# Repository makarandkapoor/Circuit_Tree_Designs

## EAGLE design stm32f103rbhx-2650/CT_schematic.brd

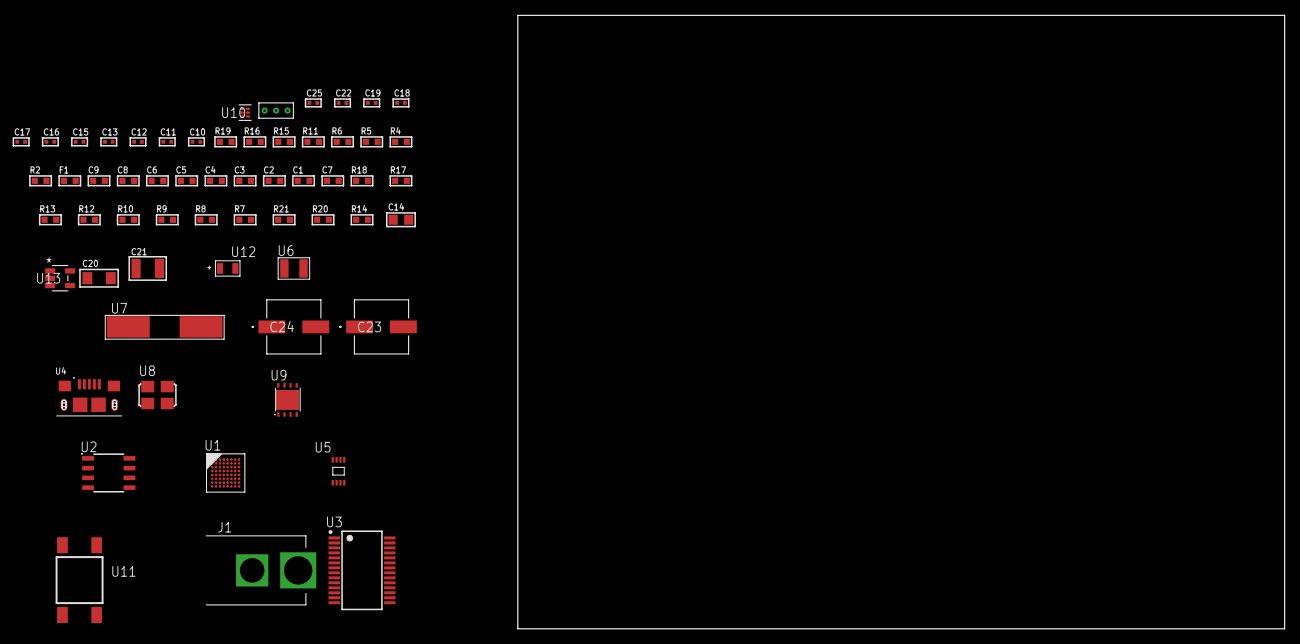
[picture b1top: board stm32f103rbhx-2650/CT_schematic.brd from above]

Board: 2 copper layers, 159.4 x 80.0 mm, 60 parts (0 on the bottom side), 35 nets, no tracks yet.

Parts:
C1, C9: 1e-06; C0603
C2, C3, C4, C5, C6: 1e-07; C0603
C7: 4.7e-06; C0603
C8: 1e-08; C0603
C10, C11: 1e-11; C0402
C12, C17, C18, C19, C25: 1e-08; C0402
C13, C15, C16, C22: 1e-07; C0402
C14: 4.7e-06; C0805
C20: 1e-05; C1206
C21: 1e-05; C1210
C23, C24: 0.0001; EXV-9H
F1: 240.0; L0603
J1: PJ-037B; PJ-037B_PACKAGE
R2, R16: 1000.0; R0603
R4, R11: 4700.0; R0603
R5, R6: 2200.0; R0603
R7, R8, R9, R10, R12, R13, R17, R18: 10000.0; R0603
R14: 100000.0; R0603
R15: 2231.0; R0603
R19: 9100.0; R0603
R20: 680000.0; R0603
R21: 120000.0; R0603
U1: stm32f103rbh6; TFBGA64
U2: AT25M02-SSHD-T; SOIC-8
U3: FT232RL-REEL; SSOP-28
U4: 10118193-0001LF; FCI_10118193-0001LF
U5: 24AA01T-I/MNY; TDFN-8/6MM
U6: ABS07-32.768KHZ-7-T
U7: ABLS-12.000MHZ-B4-T
U8: ASFL1-25MHZ-NCS; ASFL1
U9: LP3878SDX-ADJ/NOPB; WSON-8
U10: TPS3895ADRYR; SON-6
U11: 4-1437565-2; SW_4-1437565-2
U12: Q65110A2395; LGM67K-G1J2-24-Z
U13: nc7sz125m5x; NC7SZ125M5X
U14: Dummy; DUMMY_PACKAGE_127

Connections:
CLK_CRYSTAL_U1_A1: C10.1, U1.A1, U6.1
CLK_CRYSTAL_U1_B1: C11.1, U1.B1, U6.2
CLK_CRYSTAL_U3_27: U3.27, U7.1
CLK_CRYSTAL_U3_28: U3.28, U7.2
CLK_U1_C1: U1.C1, U8.3
GND: C1.2, C2.2, C3.2, C4.2, C5.2, C6.2, C7.2, C8.2, C9.2, C10.2, C11.2, C12.2, C13.2, C14.2, C15.2, C16.2, C17.2, C18.2, C19.2, C20.2, C21.2, C22.2, C23.2, C24.2, C25.2, J1.2, R2.2, R7.2, R13.2, R16.2, R19.2, R21.2, U1.C2, U1.D4, U1.D5, U1.D6, U1.F1, U2.4, U3.7, U3.18, U3.21, U3.25, U3.26, U4.5, U4.6, U4.7, U4.8, U4.9, U5.4, U5.7, U8.2, U9.3, U9.PAD, U10.2, U12.C, U13.1, U13.3, U14.1
NET_U1_A3: R6.1, U1.A3, U5.5
NET_U1_B3: R5.1, U1.B3, U5.6
NET_U1_B4: R7.1, U1.B4
NET_U1_E1: R4.1, U1.E1, U13.4
NET_U1_H1: C8.1, C9.1, F1.1, U1.G1, U1.H1
NET_U1_H8: U11.3, U11.4
NET_U2_3: R8.1, U2.3
NET_U2_7: R10.1, U2.7
NET_U3_14: R12.1, U3.14
NET_U3_17: C15.1, U3.17
NET_U3_19: R13.1, U3.19
NET_U4_1: R11.1, U4.1
NET_U4_2: U3.16, U4.2
NET_U4_3: U3.15, U4.3
NET_U9_1: C19.1, U9.1
NET_U9_6: R15.2, R16.1, U9.6
NET_U9_8: R14.1, U9.8
NET_U10_1: R18.1, R19.1, U10.1
NET_U10_3: R20.2, R21.1, U10.3
NET_U10_4: R17.1, U10.4, U13.2
NET_U11_1: R2.1, U11.1, U11.2
PROC_SPI1_MISO: U1.A4, U2.2
PROC_SPI1_MOSI: U1.C4, U2.5
PROC_SPI1_NSS: R9.1, U1.A6, U2.1
PROC_SPI1_SCK: U1.A5, U2.6
PROC_TIM1_CH2N: U1.F5, U14.2
PROC_TIM1_CH3: U1.C6, U14.3
VCC_S1_6V7: C20.1, C23.1, C24.1, J1.1, R14.2, U9.4
VCC_TIER1_3V3: C1.1, C2.1, C3.1, C4.1, C5.1, C6.1, C7.1, C12.1, C13.1, C14.1, C16.1, C17.1, C18.1, C21.1, C22.1, C25.1, F1.2, R4.2, R5.2, R6.2, R8.2, R9.2, R10.2, R12.2, R15.1, R17.2, R18.2, R20.1, U1.B2, U1.D2, U1.E4, U1.E5, U1.E6, U2.8, U3.4, U3.20, U5.8, U8.4, U9.5, U10.6, U13.5

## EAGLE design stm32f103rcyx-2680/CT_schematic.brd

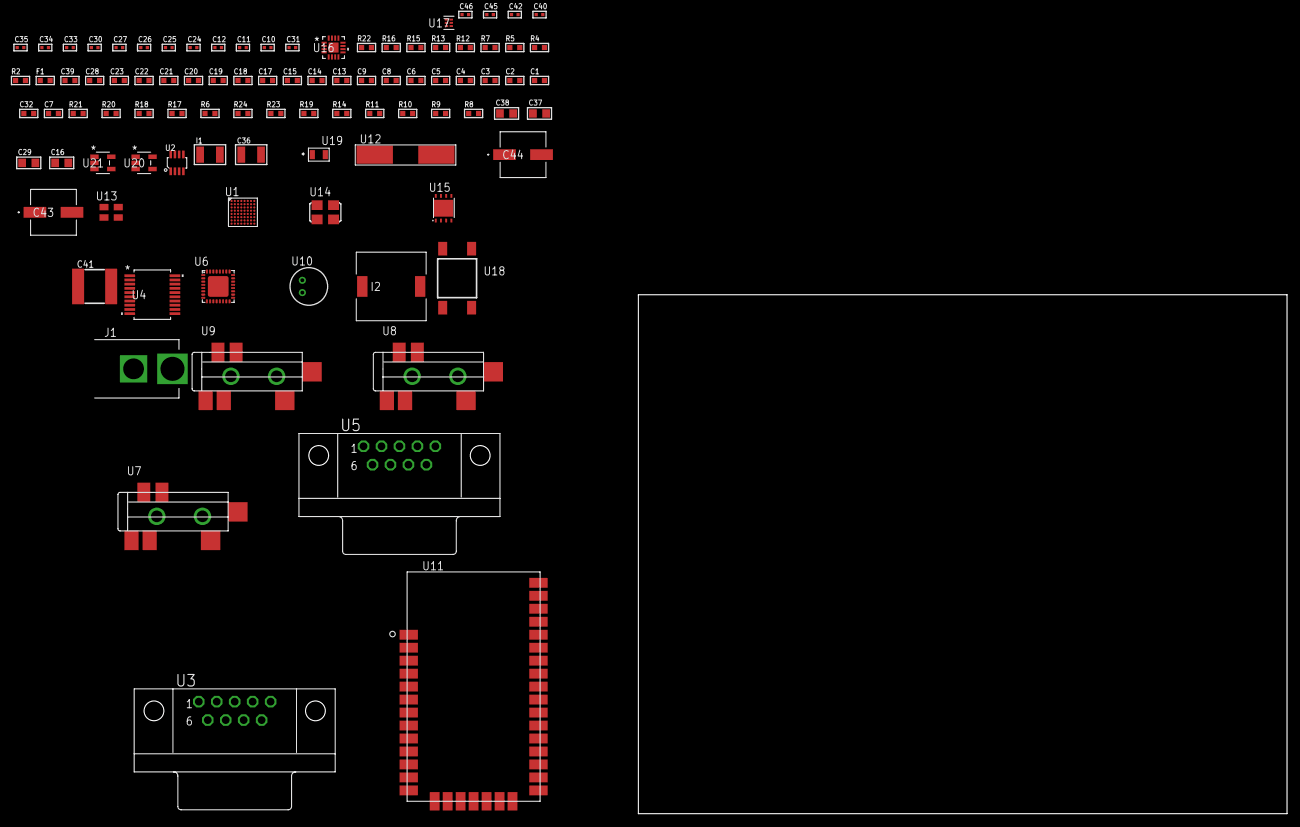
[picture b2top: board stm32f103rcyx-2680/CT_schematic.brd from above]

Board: 2 copper layers, 100.0 x 80.0 mm, 93 parts (0 on the bottom side), 66 nets, no tracks yet.

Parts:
C1, C9, C13, C14, C15, C17, C18, C19, C20, C21, C22, C23, C28, C39: 1e-06; C0603
C2, C3, C4, C5, C6: 1e-07; C0603
C7: 4.7e-06; C0603
C8: 1e-08; C0603
C10, C11: 1e-11; C0402
C12, C24, C25, C26, C27, C30, C40, C42: 1e-07; C0402
C16: 4.7e-06; C0805
C29, C37, C38: 1e-05; C0805
C31: 4.7e-11; C0402
C32: 8.2e-12; C0603
C33, C34, C35, C45, C46: 1e-08; C0402
C36: 1e-05; C1210
C41: 6.8e-05; 2220
C43, C44: 0.0001; EXV-9H
F1: 240.0; L0603
I1: 1.5e-05; L1210
I2: 5.2e-06; DR1040
J1: PJ-037B; PJ-037B_PACKAGE
R2, R16: 1000.0; R0603
R4, R5: 4700.0; R0603
R6, R20, R21: 10000.0; R0603
R7: 120.0; R0603
R8, R9, R10, R11, R14: 100000.0; R0603
R12, R13: 1270.0; R0603
R15: 200.0; R0603
R17: 20000.0; R0603
R18: 91000.0; R0603
R19: 300000.0; R0603
R22: 9100.0; R0603
R23: 680000.0; R0603
R24: 120000.0; R0603
U1: stm32f103rcy7; WLCSP64
U2: MAX3051EKA+T; SOT-23-8
U3, U5: 182-009-113R531; 182-009-MALE
U4: MAX3218EAP+T; SSOP-20
U6: SGTL5000XNAA3; QFN-32
U7, U8, U9: SJ-43515TS-SMT-TR
U10: WM-64PCT; WM-64PC
U11: XB24CZ7UIS-004
U12: ABLS-25.000MHZ-B2F-T
U13: ASEK-32.768KHz-ECST; ASEK
U14: ASFL-24.57MHZ-NCS; ASFL1
U15: LP3878SDX-ADJ/NOPB; WSON-8
U16: LTC3601EUD#PBF; QFN-16_EP
U17: TPS3895ADRYR; SON-6
U18: 4-1437565-2; SW_4-1437565-2
U19: Q65110A2395; LGM67K-G1J2-24-Z
U20, U21: nc7sz125m5x; NC7SZ125M5X

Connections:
CLK_CRYSTAL_U1_D7: C10.1, U1.D7, U12.1
CLK_CRYSTAL_U1_D8: C11.1, U1.D8, U12.2
CLK_U1_B8: U1.B8, U13.3
CLK_U6_21: U6.21, U14.3
GND: C1.2, C2.2, C3.2, C4.2, C5.2, C6.2, C7.2, C8.2, C9.2, C10.2, C11.2, C12.2, C13.2, C14.2, C15.2, C24.2, C25.2, C26.2, C27.2, C28.2, C29.2, C30.2, C31.2, C32.2, C33.2, C34.2, C35.2, C36.2, C37.2, C38.2, C39.2, C41.1, C41.2, C42.2, C43.2, C44.2, C45.2, C46.2, J1.2, R2.2, R6.2, R8.2, R13.2, R16.2, R17.2, R19.2, R22.2, R24.2, U1.A7, U1.B1, U1.E7, U1.F5, U1.H2, U2.2, U3.5, U4.5, U4.17, U4.20, U5.5, U6.1, U6.3, U6.7, U6.EXP, U8.1, U9.1, U10.2, U11.1, U11.11, U11.13, U11.22, U11.35, U13.2, U14.2, U15.3, U15.PAD, U16.1, U16.9, U16.17, U17.2, U19.C, U20.1, U20.3, U21.1, U21.3
NET_U1_A6: R6.1, U1.A6
NET_U1_C7: R5.1, U1.C7, U21.4
NET_U1_G8: C8.1, C9.1, F1.1, U1.F7, U1.G8
NET_U1_H8: U18.3, U18.4
NET_U2_6: R7.2, U2.6
NET_U2_8: R8.1, U2.8
NET_U3_2: R7.2, U2.6, U3.2
NET_U3_3: R7.1, U2.7, U3.3
NET_U4_1: I1.1, U4.1
NET_U4_2: R9.1, U4.2
NET_U4_3: R10.1, U4.3
NET_U4_4: R11.1, U4.4
NET_U4_15: C15.1, U4.15
NET_U4_16: C16.2, U4.16
NET_U4_18: C16.1, U4.18
NET_U4_19: C14.1, U4.19
NET_U5_2: U4.12, U5.2
NET_U5_3: U4.14, U5.3
NET_U5_7: U4.11, U5.7
NET_U5_8: U4.13, U5.8
NET_U6_10: C27.1, U6.10
NET_U6_29: R12.1, U6.29
NET_U6_31: R13.1, U6.31
NET_U7_1: U6.4, U7.1
NET_U7_2: U6.2, U7.2
NET_U7_5: U6.6, U7.5
NET_U8_2: C18.1, U8.2
NET_U8_5: C17.1, U8.5
NET_U9_2: C20.1, C21.1, U9.2
NET_U9_5: C19.1, U9.5
NET_U9_13: C20.2, C21.2
NET_U10_1: C22.1, C23.1, C28.1, U6.16, U10.1
NET_U10_15: C22.2, C23.2
NET_U11_6: R4.1, U11.6, U20.4
NET_U15_1: C35.1, U15.1
NET_U15_6: R15.2, R16.1, U15.6
NET_U15_8: R14.1, U15.8
NET_U16_3: C40.2, I2.1, U16.3, U16.4
NET_U16_6: C40.1, U16.6
NET_U16_7: C39.1, U16.7, U16.12
NET_U16_10: R19.1, U16.10
NET_U16_11: R17.1, R18.1, U16.11
NET_U16_ATNET_3: I2.2, R18.2
NET_U17_1: R21.1, R22.1, U17.1
NET_U17_3: R23.2, R24.1, U17.3
NET_U17_4: R20.1, U17.4, U20.2, U21.2
NET_U18_1: R2.1, U18.1, U18.2
PROC_CAN_RX: U1.C1, U2.4
PROC_CAN_TX: U1.B6, U2.1
PROC_I2S2_CK: U1.G1, U6.24
PROC_I2S2_SD: U1.F1, U6.26
PROC_I2S2_WS: U1.G2, U6.23
PROC_SPI1_MISO: U1.B4, U11.17
PROC_SPI1_MOSI: U1.A5, U11.16
PROC_SPI1_NSS: U1.C3, U11.15
PROC_SPI1_SCK: U1.A4, U11.14
PROC_UART4_RX: U1.B3, U4.9
PROC_UART4_TX: U1.A2, U4.7
VCC_S1_13V0: C36.1, C38.1, C43.1, C44.1, J1.1, R14.2, U15.4, U16.15, U16.16
VCC_TIER1_1V2: C24.1, C37.1, R15.1, U6.30, U15.5
VCC_TIER1_3V3: C1.1, C2.1, C3.1, C4.1, C5.1, C6.1, C7.1, C12.1, C13.1, C25.1, C26.1, C29.1, C30.1, C31.1, C32.1, C33.1, C34.1, C41.2, C42.1, C45.1, C46.1, F1.2, I1.2, I2.2, R4.2, R5.2, R9.2, R10.2, R11.2, R12.2, R18.2, R20.2, R21.2, R23.1, U1.A1, U1.A8, U1.C6, U1.G6, U1.H1, U2.3, U4.6, U6.5, U6.20, U11.2, U11.27, U13.4, U14.4, U16.8, U17.6, U20.5, U21.5

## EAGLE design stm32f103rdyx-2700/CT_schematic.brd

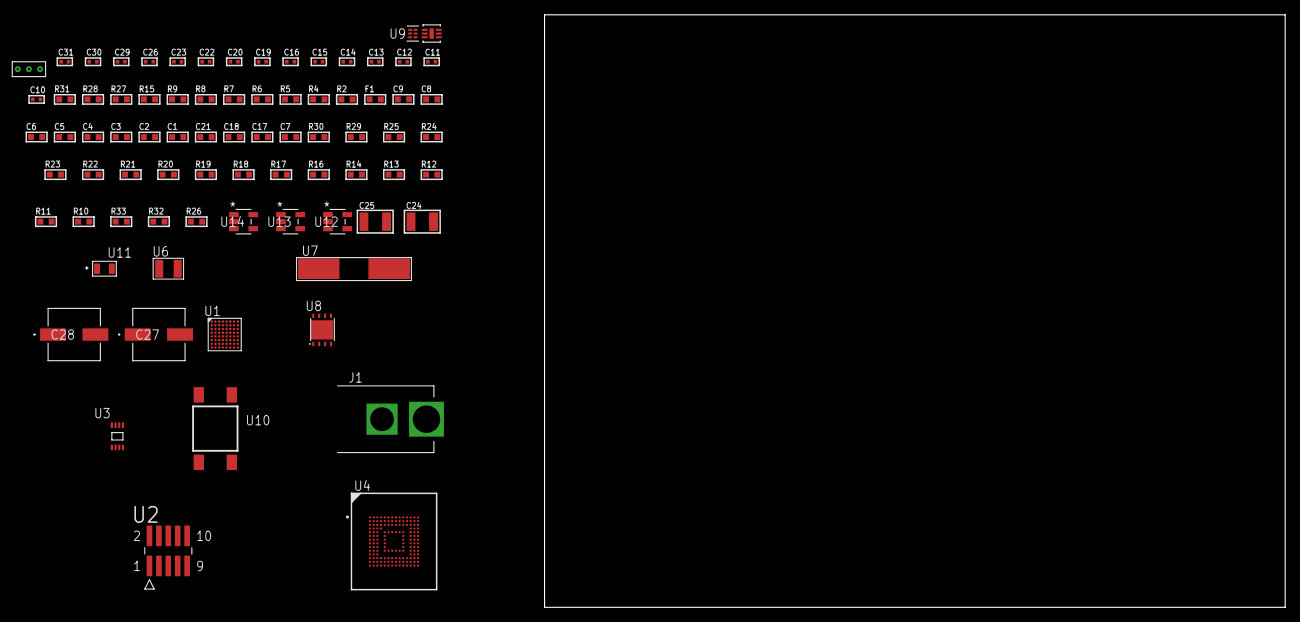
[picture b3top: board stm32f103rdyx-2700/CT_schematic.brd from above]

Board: 2 copper layers, 100.0 x 80.0 mm, 79 parts (0 on the bottom side), 42 nets, no tracks yet.

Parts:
C1, C9: 1e-06; C0603
C2, C3, C4, C5, C6: 1e-07; C0603
C7: 4.7e-06; C0603
C8: 1e-08; C0603
C10, C11, C12, C13: 1e-11; C0402
C14, C16, C19, C20, C22, C26: 1e-07; C0402
C15, C23, C29, C30, C31: 1e-08; C0402
C17, C18, C21: 2.2e-06; C0603
C24, C25: 1e-05; C1210
C27, C28: 0.0001; EXV-9H
F1: 240.0; L0603
J1: PJ-037B; PJ-037B_PACKAGE
R2, R28: 1000.0; R0603
R4, R5: 4700.0; R0603
R6, R7, R8, R9: 2200.0; R0603
R10, R11, R12, R13, R14, R29, R30: 10000.0; R0603
R15: 5.0; R0603
R16, R17, R18, R19, R20, R21, R22, R23, R24, R25: 34000.0; R0603
R26: 100000.0; R0603
R27: 2231.0; R0603
R31: 9100.0; R0603
R32: 680000.0; R0603
R33: 120000.0; R0603
U1: stm32f103rdy6; WLCSP64
U2: FTSH-105-01-L-DV-K; SAMTEC_FTSH-105-01-L-DV-K
U3: 24AA16-I/MC; TDFN-8/6MM
U4: mtfc4gmcdm; TFBGA-153
U5: Si7051-A20-IM; DFN-6
U6: ABS07-32.768KHZ-7-T
U7: ABLS-25.000MHZ-B2F-T
U8: LP3878SDX-ADJ/NOPB; WSON-8
U9: TPS3895ADRYR; SON-6
U10: 4-1437565-2; SW_4-1437565-2
U11: Q65110A2395; LGM67K-G1J2-24-Z
U12, U13, U14: nc7sz125m5x; NC7SZ125M5X
U15: Dummy; DUMMY_PACKAGE_181

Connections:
CLK_CRYSTAL_U1_B7: C10.1, U1.B7, U6.1
CLK_CRYSTAL_U1_B8: C11.1, U1.B8, U6.2
CLK_CRYSTAL_U1_D7: C12.1, U1.D7, U7.1
CLK_CRYSTAL_U1_D8: C13.1, U1.D8, U7.2
GND: C1.2, C2.2, C3.2, C4.2, C5.2, C6.2, C7.2, C8.2, C9.2, C10.2, C11.2, C12.2, C13.2, C14.2, C15.2, C16.2, C17.2, C18.2, C19.2, C20.2, C21.2, C22.2, C23.2, C24.2, C25.2, C26.2, C27.2, C28.2, C29.2, C30.2, C31.2, J1.2, R2.2, R10.2, R14.2, R15.2, R28.2, R31.2, R33.2, U1.A7, U1.B1, U1.E7, U1.F5, U1.H2, U2.3, U2.5, U3.4, U4.C4, U4.E7, U4.G5, U4.H10, U4.K8, U4.N2, U4.N5, U4.P4, U4.P6, U5.2, U5.7, U8.3, U8.PAD, U9.2, U11.C, U12.2, U12.3, U13.1, U13.3, U14.1, U14.3, U15.1
NET_U1_A6: R10.1, U1.A6
NET_U1_B5: R6.1, U1.B5, U5.6
NET_U1_C5: R7.1, U1.C5, U5.1
NET_U1_C7: R5.1, U1.C7, U14.4
NET_U1_F3: R9.1, U1.F3, U3.5
NET_U1_G3: R8.1, U1.G3, U3.6
NET_U1_G8: C8.1, C9.1, F1.1, U1.F7, U1.G8
NET_U1_H8: U10.3, U10.4
NET_U2_2: R13.1, U2.2
NET_U2_4: R14.1, U2.4
NET_U2_9: R15.1, U2.9
NET_U4_C2: C18.1, C19.1, U4.C2
NET_U4_K5: R4.1, U4.K5, U13.4
NET_U8_1: C23.1, U8.1
NET_U8_6: R27.2, R28.1, U8.6
NET_U8_8: R26.1, U8.8
NET_U9_1: R30.1, R31.1, U9.1
NET_U9_3: R32.2, R33.1, U9.3
NET_U9_4: R29.1, U9.4, U12.4, U13.2, U14.2
NET_U10_1: R2.1, U10.1, U10.2
PROC_ADC1_IN1: U1.E6, U15.2
PROC_ADC1_IN3: U1.G7, U15.3
PROC_SDIO_CK: R25.1, U1.C4, U4.M6
PROC_SDIO_CMD: R24.1, U1.A3, U4.M5
PROC_SDIO_D0: R16.1, U1.E3, U4.A3
PROC_SDIO_D1: R17.1, U1.D1, U4.A4
PROC_SDIO_D2: R18.1, U1.A2, U4.A5
PROC_SDIO_D3: R19.1, U1.B3, U4.B2
PROC_SDIO_D4: R20.1, U1.D5, U4.B3
PROC_SDIO_D5: R21.1, U1.B6, U4.B4
PROC_SDIO_D6: R22.1, U1.E1, U4.B5
PROC_SDIO_D7: R23.1, U1.E2, U4.B6
PROC_SYS_JTDI: R12.1, U1.C3, U2.8
PROC_SYS_JTDO_TRACESWO: U1.A4, U2.6
RST_OUT_U2_JTAG_RST_B: R11.1, U2.10, U12.1
VCC_S1_15V2: C24.1, C27.1, C28.1, J1.1, R26.2, U8.4
VCC_TIER1_3V3: C1.1, C2.1, C3.1, C4.1, C5.1, C6.1, C7.1, C14.1, C15.1, C16.1, C17.1, C20.1, C21.1, C22.1, C25.1, C26.1, C29.1, C30.1, C31.1, F1.2, R4.2, R5.2, R6.2, R7.2, R8.2, R9.2, R11.2, R12.2, R13.2, R16.2, R17.2, R18.2, R19.2, R20.2, R21.2, R22.2, R23.2, R24.2, R25.2, R27.1, R29.2, R30.2, R32.1, U1.A1, U1.A8, U1.C6, U1.G6, U1.H1, U2.1, U3.7, U3.8, U4.C6, U4.E6, U4.F5, U4.J10, U4.K9, U4.M4, U4.N4, U4.P3, U4.P5, U5.5, U8.5, U9.6, U12.5, U13.5, U14.5

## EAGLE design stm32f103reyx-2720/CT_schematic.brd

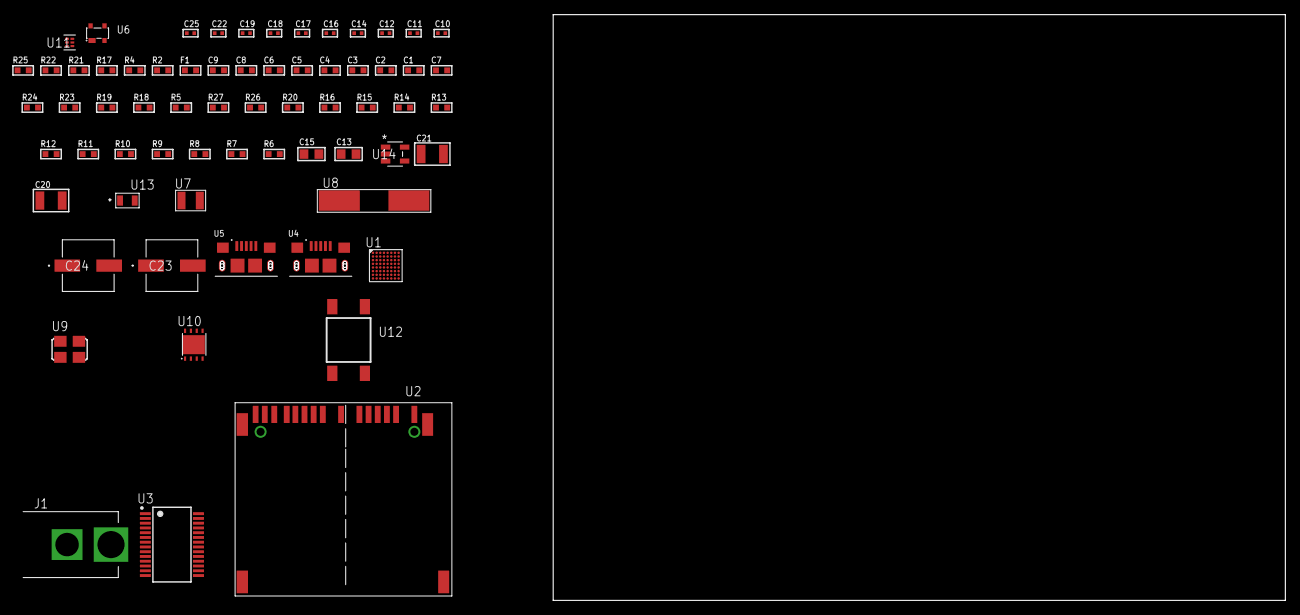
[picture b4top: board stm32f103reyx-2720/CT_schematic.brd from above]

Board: 2 copper layers, 66 parts (0 on the bottom side), 44 nets, no tracks yet.

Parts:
C1, C9: 1e-06; C0603
C2, C3, C4, C5, C6: 1e-07; C0603
C7: 4.7e-06; C0603
C8: 1e-08; C0603
C10, C11: 1e-11; C0402
C12, C14, C16, C17, C22: 1e-07; C0402
C13: 1e-05; C0805
C15: 4.7e-06; C0805
C18, C19, C25: 1e-08; C0402
C20, C21: 1e-05; C1210
C23, C24: 0.0001; EXV-9H
F1: 240.0; L0603
J1: PJ-037B; PJ-037B_PACKAGE
R2, R22: 1000.0; R0603
R4, R17: 4700.0; R0603
R5, R18, R19, R23, R24: 10000.0; R0603
R6, R7, R8, R9, R10, R11, R12, R13, R14, R15, R16, R20: 100000.0; R0603
R21: 2231.0; R0603
R25: 9100.0; R0603
R26: 680000.0; R0603
R27: 120000.0; R0603
U1: stm32f103rey7; WLCSP64
U2: 10100565
U3: FT232RL-REEL; SSOP-28
U4, U5: 10118193-0001LF; FCI_10118193-0001LF
U6: prtr5v0u2ax; SOT143B
U7: ABS07-32.768KHZ-7-T
U8: ABLS-12.000MHZ-B4-T
U9: ASFL1-25MHZ-NCS; ASFL1
U10: LP3878SDX-ADJ/NOPB; WSON-8
U11: TPS3895ADRYR; SON-6
U12: 4-1437565-2; SW_4-1437565-2
U13: Q65110A2395; LGM67K-G1J2-24-Z
U14: nc7sz125m5x; NC7SZ125M5X

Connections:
CLK_CRYSTAL_U1_B7: C10.1, U1.B7, U7.1
CLK_CRYSTAL_U1_B8: C11.1, U1.B8, U7.2
CLK_CRYSTAL_U3_27: U3.27, U8.1
CLK_CRYSTAL_U3_28: U3.28, U8.2
CLK_U1_D8: U1.D8, U9.3
GND: C1.2, C2.2, C3.2, C4.2, C5.2, C6.2, C7.2, C8.2, C9.2, C10.2, C11.2, C12.2, C13.2, C14.2, C15.2, C16.2, C17.2, C18.2, C19.2, C20.2, C21.2, C22.2, C23.2, C24.2, C25.2, J1.2, R2.2, R5.2, R19.2, R22.2, R25.2, R27.2, U1.A7, U1.B1, U1.E7, U1.F5, U1.H2, U2.6, U2.10, U2.12, U2.16, U2.17, U2.20, U2.21, U3.7, U3.18, U3.21, U3.25, U3.26, U4.5, U4.6, U4.7, U4.8, U4.9, U5.5, U5.6, U5.7, U5.8, U5.9, U6.1, U9.2, U10.3, U10.PAD, U11.2, U13.C, U14.1, U14.3
NET_U1_A6: R5.1, U1.A6
NET_U1_C7: R4.1, U1.C7, U14.4
NET_U1_G8: C8.1, C9.1, F1.1, U1.F7, U1.G8
NET_U1_H7: U12.3, U12.4
NET_U2_1: R8.1, U2.1
NET_U2_2: R7.1, U2.2
NET_U2_18: U2.18, U2.19
NET_U3_14: R18.1, U3.14
NET_U3_17: C16.1, U3.17
NET_U3_19: R19.1, U3.19
NET_U4_1: R17.1, U4.1
NET_U4_2: U3.16, U4.2
NET_U4_3: U3.15, U4.3
NET_U6_4: U5.1, U6.4
NET_U10_1: C19.1, U10.1
NET_U10_6: R21.2, R22.1, U10.6
NET_U10_8: R20.1, U10.8
NET_U11_1: R24.1, R25.1, U11.1
NET_U11_3: R26.2, R27.1, U11.3
NET_U11_4: R23.1, U11.4, U14.2
NET_U12_1: R2.1, U12.1, U12.2
PROC_SDIO_CK: R6.1, U1.C4, U2.8
PROC_SDIO_D0: R9.1, U1.E3, U2.4
PROC_SDIO_D1: R10.1, U1.D1, U2.3
PROC_SDIO_D2: R11.1, U1.A2, U2.15
PROC_SDIO_D3: R12.1, U1.B3, U2.14
PROC_SDIO_D4: R13.1, U1.D5, U2.13
PROC_SDIO_D5: R14.1, U1.B6, U2.11
PROC_SDIO_D6: R15.1, U1.E1, U2.7
PROC_SDIO_D7: R16.1, U1.E2, U2.5
PROC_USART2_CTS: U1.F6, U3.3
PROC_USART2_RTS: U1.E6, U3.11
PROC_USART2_RX: U1.G7, U3.1
PROC_USART2_TX: U1.H8, U3.5
PROC_USB_DM: U1.C1, U5.2, U6.3
PROC_USB_DP: U1.C2, U5.3, U6.2
VCC_S1_15V6: C20.1, C23.1, C24.1, J1.1, R20.2, U10.4
VCC_TIER1_3V3: C1.1, C2.1, C3.1, C4.1, C5.1, C6.1, C7.1, C12.1, C13.1, C14.1, C15.1, C17.1, C18.1, C21.1, C22.1, C25.1, F1.2, R4.2, R6.2, R7.2, R8.2, R9.2, R10.2, R11.2, R12.2, R13.2, R14.2, R15.2, R16.2, R18.2, R21.1, R23.2, R24.2, R26.1, U1.A1, U1.A8, U1.C6, U1.G6, U1.H1, U2.9, U3.4, U3.20, U9.4, U10.5, U11.6, U14.5

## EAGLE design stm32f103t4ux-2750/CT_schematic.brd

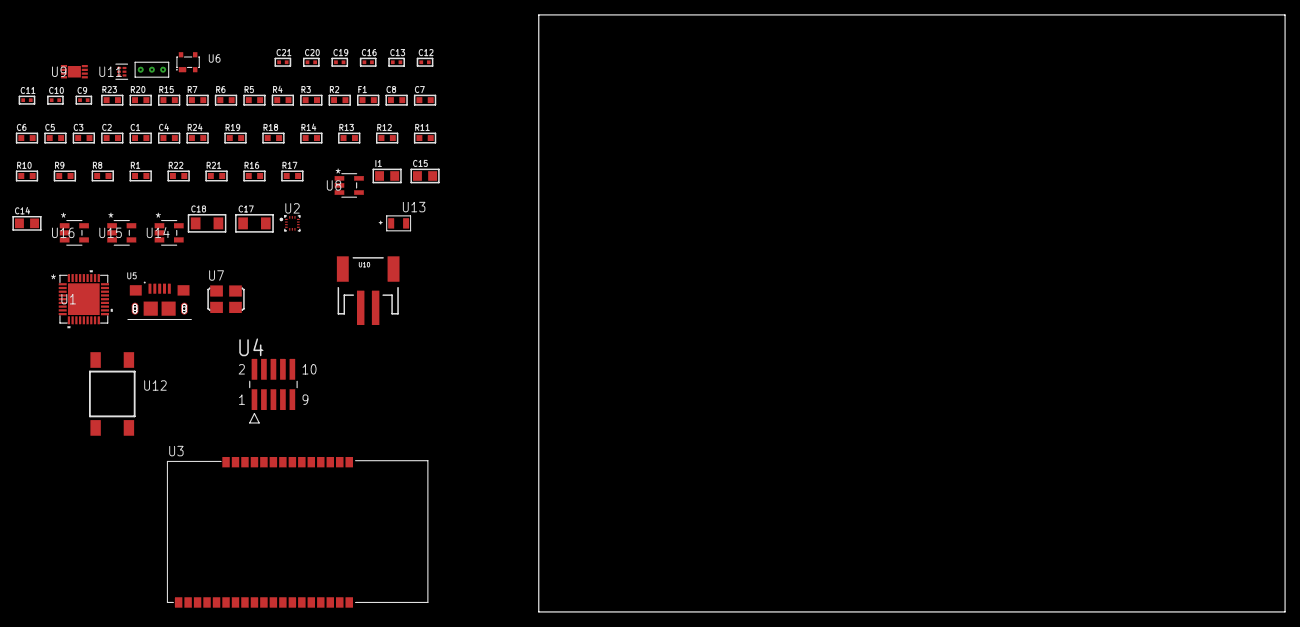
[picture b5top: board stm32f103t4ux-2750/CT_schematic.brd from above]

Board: 2 copper layers, 64 parts (0 on the bottom side), 37 nets, no tracks yet.

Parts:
C1, C2, C3, C5, C6: 1e-07; C0603
C4: 4.7e-06; C0603
C7: 1e-08; C0603
C8: 1e-06; C0603
C9, C10, C11, C12, C16: 1e-07; C0402
C13, C19, C20, C21: 1e-08; C0402
C14, C15: 1e-05; C0805
C17, C18: 1e-05; C1206
F1: 240.0; L0603
I1: 2.2e-06; L0805
R1, R8, R9, R10, R11, R12, R13, R14, R18, R19, R24: 10000.0; R0603
R2: 1000.0; R0603
R3: 1600.5; R0603
R4, R5: 4700.0; R0603
R6, R7: 2200.0; R0603
R15: 5.0; R0603
R16: 220000.0; R0603
R17: 1000000.0; R0603
R20: 9100.0; R0603
R21: 680000.0; R0603
R22: 120000.0; R0603
R23: 2000.0; R0603
U1: stm32f103t4u6; VFQFPN36
U2: BMC150; LGA14R35P5X6_200X200X100
U3: ETRX3587
U4: FTSH-105-01-L-DV-K; SAMTEC_FTSH-105-01-L-DV-K
U5: 10118193-0001LF; FCI_10118193-0001LF
U6: prtr5v0u2ax; SOT143B
U7: ASFL1-25MHZ-NCS; ASFL1
U8: ltc3406es5; TSOT-23-5
U9: MCP73831T-2ACI/MC; DFN8_2X3MC
U10: S2B-PH-SM4-TB(LF)(SN); JST-2-SMD
U11: TPS3895ADRYR; SON-6
U12: 4-1437565-2; SW_4-1437565-2
U13: Q65110A2395; LGM67K-G1J2-24-Z
U14, U15, U16: nc7sz125m5x; NC7SZ125M5X
U17: Dummy; DUMMY_PACKAGE_141

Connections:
CLK_U1_2: U1.2, U7.3
GND: C1.2, C2.2, C3.2, C4.2, C5.2, C6.2, C7.2, C8.2, C9.2, C10.2, C11.2, C12.2, C13.2, C14.2, C15.1, C15.2, C16.2, C17.2, C18.2, C19.2, C20.2, C21.2, R2.2, R8.2, R10.2, R14.2, R15.2, R16.2, R20.2, R22.2, R23.2, U1.5, U1.18, U1.26, U1.36, U1.37, U2.1, U2.6, U2.7, U2.9, U3.1, U3.13, U3.19, U3.20, U3.31, U3.33, U4.3, U4.5, U5.5, U5.6, U5.7, U5.8, U5.9, U6.1, U7.2, U8.2, U9.6, U9.9, U10.2, U11.2, U13.C, U14.2, U14.3, U15.1, U15.3, U16.1, U16.3, U17.1
INPUT_USBPOWER_5V: C17.1, R24.2, U5.1, U6.4, U9.1, U9.2
NET_U1_4: R5.1, U1.4, U16.4
NET_U1_6: C7.1, C8.1, F1.1, U1.6
NET_U1_31: R3.1, U1.31, U13.A
NET_U1_32: R1.1, U1.32, U12.3, U12.4
NET_U1_33: R6.1, U1.33, U2.11
NET_U1_34: R7.1, U1.34, U2.14
NET_U1_35: R8.1, U1.35
NET_U3_7: R4.1, U3.7, U15.4
NET_U3_21: R10.1, U3.21
NET_U4_2: R13.1, U4.2
NET_U4_4: R14.1, U4.4
NET_U4_9: R15.1, U4.9
NET_U8_3: I1.1, U8.3
NET_U8_5: R16.1, R17.1, U8.5
NET_U8_ATNET_3: I1.2, R17.2
NET_U9_5: R24.1, U9.5
NET_U9_8: R23.1, U9.8
NET_U11_1: R19.1, R20.1, U11.1
NET_U11_3: R21.2, R22.1, U11.3
NET_U11_4: R18.1, U11.4, U14.4, U15.2, U16.2
NET_U12_1: R2.1, U12.1, U12.2
PROC_ADC1_IN4: U1.11, U17.2
PROC_ADC1_IN7: U1.14, U17.3
PROC_SYS_JTDI: R12.1, U1.29, U4.8
PROC_SYS_JTDO_TRACESWO: U1.30, U4.6
PROC_USART2_CTS: U1.7, U3.8
PROC_USART2_RTS: U1.8, U3.6
PROC_USART2_RX: U1.10, U3.17
PROC_USART2_TX: U1.9, U3.18
PROC_USB_DM: U1.23, U5.2, U6.3
PROC_USB_DP: U1.24, U5.3, U6.2
RST_OUT_U4_JTAG_RST_B: R11.1, U4.10, U14.1
VCC_S1_3V7: C14.1, C18.1, U8.4, U9.3, U9.4, U10.1
VCC_TIER1_3V3: C1.1, C2.1, C3.1, C4.1, C5.1, C6.1, C9.1, C10.1, C11.1, C12.1, C13.1, C15.2, C16.1, C19.1, C20.1, C21.1, F1.2, I1.2, R1.2, R3.2, R4.2, R5.2, R6.2, R7.2, R9.1, R9.2, R11.2, R12.2, R13.2, R17.2, R18.2, R19.2, R21.1, U1.1, U1.19, U1.27, U2.8, U2.10, U2.12, U2.13, U3.32, U4.1, U7.4, U11.6, U14.5, U15.5, U16.5

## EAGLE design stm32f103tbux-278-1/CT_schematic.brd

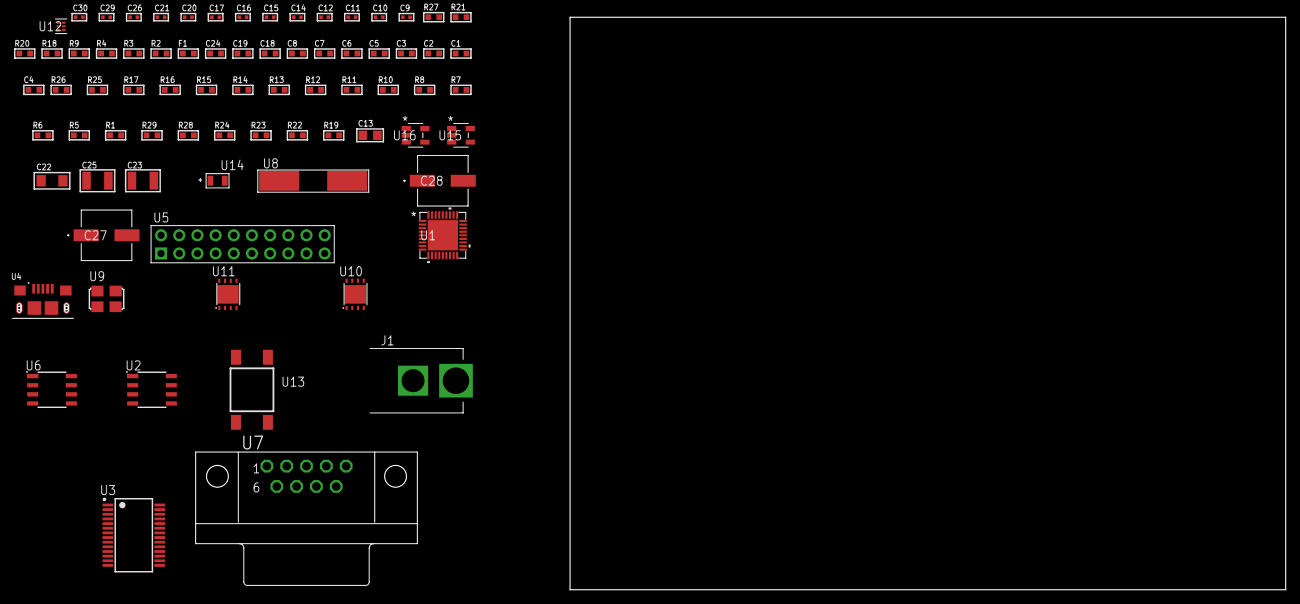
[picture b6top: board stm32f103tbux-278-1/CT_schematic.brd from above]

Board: 2 copper layers, 177.2 x 80.0 mm, 77 parts (0 on the bottom side), 49 nets, no tracks yet.

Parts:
C1, C2, C3, C5, C6: 1e-07; C0603
C4: 4.7e-06; C0603
C7: 1e-08; C0603
C8, C18, C19, C24: 1e-06; C0603
C9, C10: 1e-11; C0402
C11, C20, C21, C29, C30: 1e-08; C0402
C12, C14, C15, C16, C17, C26: 1e-07; C0402
C13: 4.7e-06; C0805
C22: 1e-05; C1206
C23, C25: 1e-05; C1210
C27, C28: 0.0001; EXV-9H
F1: 240.0; L0603
J1: PJ-037B; PJ-037B_PACKAGE
R1, R5, R6, R7, R8, R10, R11, R12, R13, R14, R15, R16, R17, R25, R26: 10000.0; R0603
R2, R21: 1000.0; R0603
R3: 1600.5; R0603
R4, R9: 4700.0; R0603
R18: 120.0; R0603
R19, R22, R24: 100000.0; R0603
R20: 2231.0; R0603
R23: 300000.0; R0603
R27: 9100.0; R0603
R28: 680000.0; R0603
R29: 120000.0; R0603
U1: stm32f103tbu6; VFQFPN36
U2: AT25512N-SH-T; SOIC-8
U3: FT232RL-REEL; SSOP-28
U4: 10118193-0001LF; FCI_10118193-0001LF
U5: TST-110-05-T-D-RA
U6: MCP2562-E/SN; SOIC-8
U7: 182-009-113R531; 182-009-MALE
U8: ABLS-25.000MHZ-B2F-T
U9: ASFL1-12MHZ-NCS; ASFL1
U10: LP3878SDX-ADJ/NOPB; WSON-8
U11: LP2951ACSDX/NOPB; WSON-8
U12: TPS3895ADRYR; SON-6
U13: 4-1437565-2; SW_4-1437565-2
U14: Q65110A2395; LGM67K-G1J2-24-Z
U15, U16: nc7sz125m5x; NC7SZ125M5X

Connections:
CLK_CRYSTAL_U1_2: C9.1, U1.2, U8.1
CLK_CRYSTAL_U1_3: C10.1, U1.3, U8.2
CLK_U3_27: U3.27, U9.3
GND: C1.2, C2.2, C3.2, C4.2, C5.2, C6.2, C7.2, C8.2, C9.2, C10.2, C11.2, C12.2, C13.2, C14.2, C15.2, C16.2, C17.2, C18.2, C19.2, C20.2, C21.2, C22.2, C23.2, C24.2, C25.2, C26.2, C27.2, C28.2, C29.2, C30.2, J1.2, R2.2, R5.2, R11.2, R17.2, R21.2, R24.2, R27.2, R29.2, U1.5, U1.18, U1.26, U1.36, U1.37, U2.4, U3.7, U3.18, U3.21, U3.25, U3.26, U4.5, U4.6, U4.7, U4.8, U4.9, U5.4, U5.6, U5.8, U5.10, U5.12, U5.14, U5.16, U5.18, U5.20, U6.2, U6.8, U7.5, U9.2, U10.3, U10.PAD, U11.3, U11.4, U11.PAD, U12.2, U14.C, U15.2, U15.3, U16.1, U16.3
NET_U1_4: R4.1, U1.4, U16.4
NET_U1_6: C7.1, C8.1, F1.1, U1.6
NET_U1_33: R3.1, U1.33, U14.A
NET_U1_34: R1.1, U1.34, U13.3, U13.4
NET_U1_35: R5.1, U1.35
NET_U2_3: R6.1, U2.3
NET_U2_7: R8.1, U2.7
NET_U3_14: R10.1, U3.14
NET_U3_17: C14.1, U3.17
NET_U3_19: R11.1, U3.19
NET_U4_1: R9.1, U4.1
NET_U4_2: U3.16, U4.2
NET_U4_3: U3.15, U4.3
NET_U5_3: R12.1, U5.3
NET_U5_7: R14.1, U5.7
NET_U5_9: R15.1, U5.9
NET_U5_19: R17.1, U5.19
NET_U6_6: R18.2, U6.6
NET_U7_2: R18.2, U6.6, U7.2
NET_U7_3: R18.1, U6.7, U7.3
NET_U10_1: C21.1, U10.1
NET_U10_6: R20.2, R21.1, U10.6
NET_U10_8: R19.1, U10.8
NET_U11_5: R22.1, U11.5
NET_U11_7: R23.2, R24.1, U11.7
NET_U12_1: R26.1, R27.1, U12.1
NET_U12_3: R28.2, R29.1, U12.3
NET_U12_4: R25.1, U12.4, U15.4, U16.2
NET_U13_1: R2.1, U13.1, U13.2
PROC_CAN_RX: U1.23, U6.4
PROC_CAN_TX: U1.24, U6.1
PROC_SPI1_MISO: U1.13, U2.2
PROC_SPI1_MOSI: U1.14, U2.5
PROC_SPI1_NSS: R7.1, U1.11, U2.1
PROC_SPI1_SCK: U1.12, U2.6
PROC_SYS_JTDI: R13.1, U1.29, U5.5
PROC_SYS_JTDO_TRACESWO: U1.30, U5.13
PROC_USART2_CTS: U1.7, U3.3
PROC_USART2_RTS: U1.8, U3.11
PROC_USART2_RX: U1.10, U3.1
PROC_USART2_TX: U1.9, U3.5
RST_OUT_U5_SRESET_B: R16.1, U5.15, U15.1
VCC_S1_9V1: C22.1, C24.1, C27.1, C28.1, J1.1, R19.2, U10.4, U11.8
VCC_TIER1_3V3: C1.1, C2.1, C3.1, C4.1, C5.1, C6.1, C11.1, C12.1, C13.1, C15.1, C16.1, C17.1, C19.1, C20.1, C23.1, C26.1, C29.1, C30.1, F1.2, R1.2, R3.2, R4.2, R6.2, R7.2, R8.2, R10.2, R12.2, R13.2, R14.2, R15.2, R16.2, R20.1, R25.2, R26.2, R28.1, U1.1, U1.19, U1.27, U2.8, U3.4, U3.20, U5.1, U5.2, U6.5, U9.4, U10.5, U12.6, U15.5, U16.5
VCC_TIER1_5V0: C18.1, C25.1, R22.2, R23.1, U6.3, U11.1

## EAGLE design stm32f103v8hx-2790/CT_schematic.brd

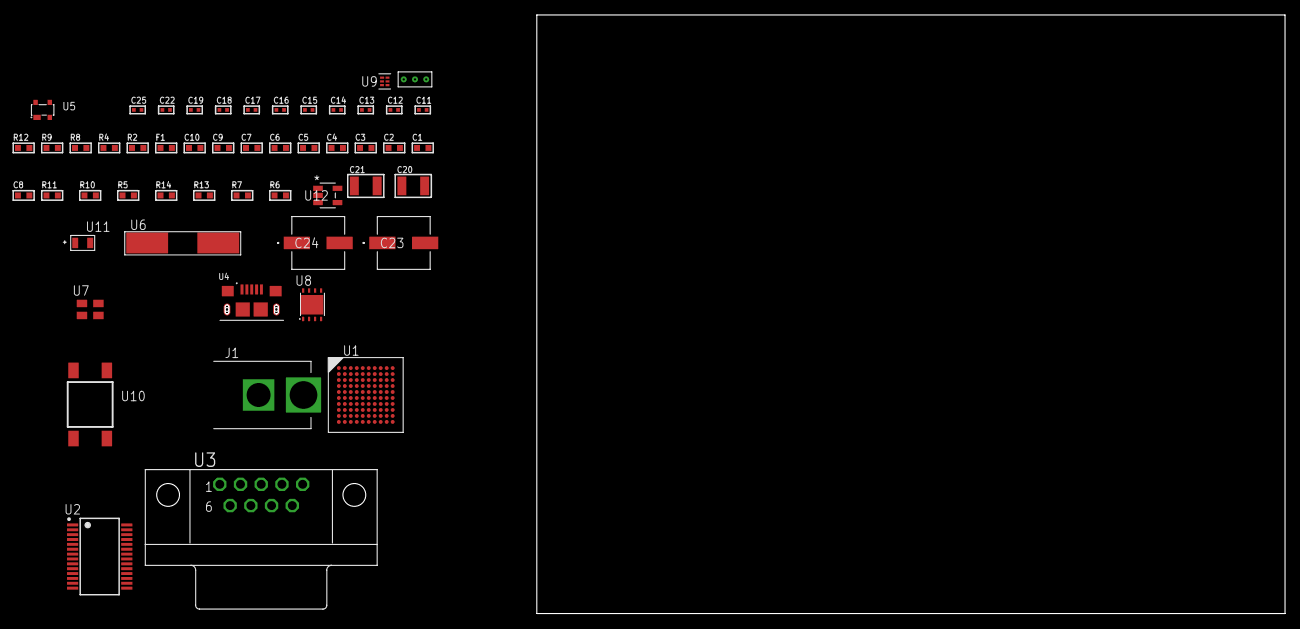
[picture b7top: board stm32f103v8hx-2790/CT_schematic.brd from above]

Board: 2 copper layers, 52 parts (0 on the bottom side), 37 nets, no tracks yet.

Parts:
C1, C10: 1e-06; C0603
C2, C3, C4, C5, C6, C7: 1e-07; C0603
C8: 4.7e-06; C0603
C9: 1e-08; C0603
C11, C12: 1e-11; C0402
C13, C14, C15, C16, C17, C22: 1e-07; C0402
C18, C19, C25: 1e-08; C0402
C20, C21: 1e-05; C1210
C23, C24: 0.0001; EXV-9H
F1: 240.0; L0603
J1: PJ-037B; PJ-037B_PACKAGE
R2, R9: 1000.0; R0603
R4: 4700.0; R0603
R5, R10, R11: 10000.0; R0603
R6, R7: 100000.0; R0603
R8: 2231.0; R0603
R12: 9100.0; R0603
R13: 680000.0; R0603
R14: 120000.0; R0603
U1: stm32f103v8h7; LFBGA100
U2: ST3241EBPR; SSOP-28
U3: 182-009-113R531; 182-009-MALE
U4: 10118193-0001LF; FCI_10118193-0001LF
U5: prtr5v0u2ax; SOT143B
U6: ABLS-25.000MHZ-B2F-T
U7: ASEK-32.768KHz-ECST; ASEK
U8: LP3878SDX-ADJ/NOPB; WSON-8
U9: TPS3895ADRYR; SON-6
U10: 4-1437565-2; SW_4-1437565-2
U11: Q65110A2395; LGM67K-G1J2-24-Z
U12: nc7sz125m5x; NC7SZ125M5X
U13: Dummy; DUMMY_PACKAGE_110

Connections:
CLK_CRYSTAL_U1_C1: C11.1, U1.C1, U6.1
CLK_CRYSTAL_U1_D1: C12.1, U1.D1, U6.2
CLK_U1_A1: U1.A1, U7.3
GND: C1.2, C2.2, C3.2, C4.2, C5.2, C6.2, C7.2, C8.2, C9.2, C10.2, C11.2, C12.2, C13.2, C16.2, C17.2, C18.2, C19.2, C20.2, C21.2, C22.2, C23.2, C24.2, C25.2, J1.2, R2.2, R5.2, R9.2, R12.2, R14.2, U1.C2, U1.E4, U1.E5, U1.E6, U1.E7, U1.G1, U1.H1, U2.23, U2.25, U3.5, U4.5, U4.6, U4.7, U4.8, U4.9, U5.1, U7.2, U8.3, U8.PAD, U9.2, U11.C, U12.1, U12.3, U13.1
NET_U1_D5: R5.1, U1.D5
NET_U1_E1: R4.1, U1.E1, U12.4
NET_U1_K1: C9.1, C10.1, F1.1, U1.J1, U1.K1
NET_U1_K10: U10.3, U10.4
NET_U2_1: C15.1, U2.1
NET_U2_2: C15.2, U2.2
NET_U2_3: C17.1, U2.3
NET_U2_22: R6.1, U2.22
NET_U2_24: C14.2, U2.24
NET_U2_27: C16.1, U2.27
NET_U2_28: C14.1, U2.28
NET_U3_2: U2.4, U3.2
NET_U3_3: U2.9, U3.3
NET_U3_7: U2.5, U3.7
NET_U3_8: U2.10, U3.8
NET_U5_4: U4.1, U5.4
NET_U8_1: C19.1, U8.1
NET_U8_6: R8.2, R9.1, U8.6
NET_U8_8: R7.1, U8.8
NET_U9_1: R11.1, R12.1, U9.1
NET_U9_3: R13.2, R14.1, U9.3
NET_U9_4: R10.1, U9.4, U12.2
NET_U10_1: R2.1, U10.1, U10.2
PROC_ADC1_IN1: U1.H2, U13.3
PROC_ADC1_IN2: U1.J2, U13.2
PROC_USART2_CTS: U1.C7, U2.13
PROC_USART2_RTS: U1.D7, U2.18
PROC_USART2_RX: U1.C6, U2.19
PROC_USART2_TX: U1.B6, U2.14
PROC_USB_DM: U1.C10, U4.2, U5.3
PROC_USB_DP: U1.B10, U4.3, U5.2
VCC_S1_14V8: C20.1, C23.1, C24.1, J1.1, R7.2, U8.4
VCC_TIER1_3V3: C1.1, C2.1, C3.1, C4.1, C5.1, C6.1, C7.1, C8.1, C13.1, C18.1, C21.1, C22.1, C25.1, F1.2, R4.2, R6.2, R8.1, R10.2, R11.2, R13.1, U1.B2, U1.D2, U1.F4, U1.F5, U1.F6, U1.F7, U2.26, U7.4, U8.5, U9.6, U12.5

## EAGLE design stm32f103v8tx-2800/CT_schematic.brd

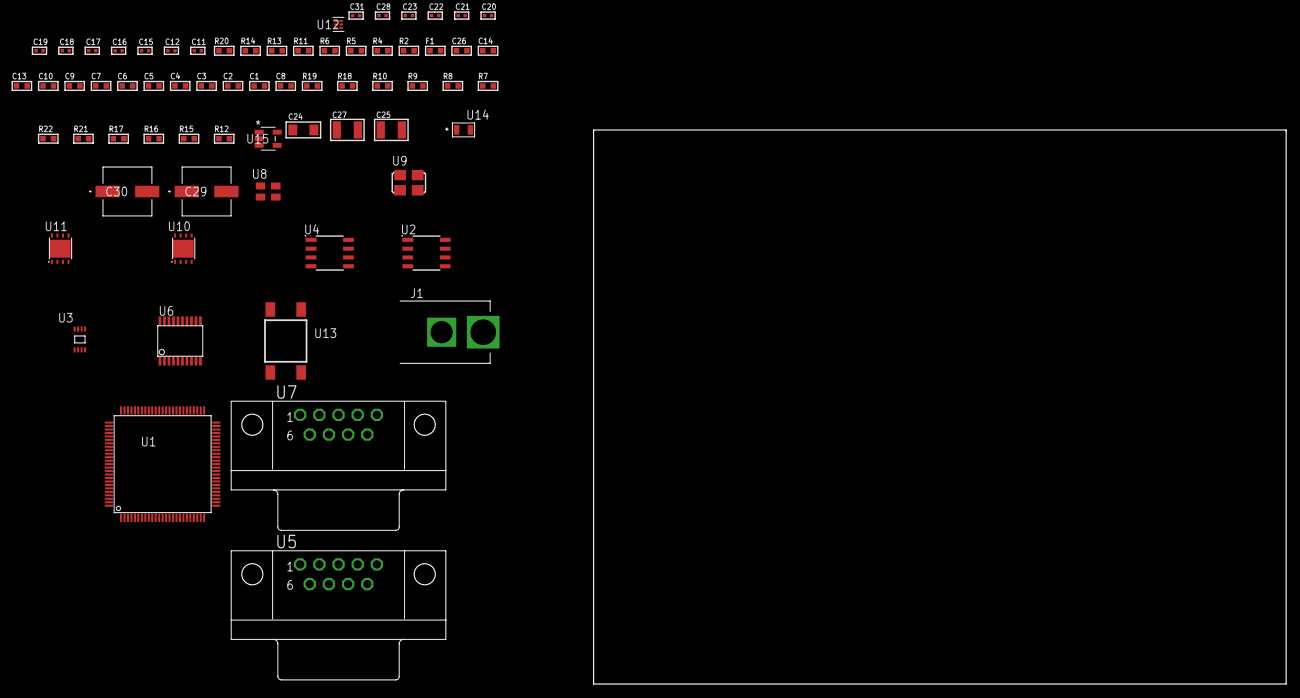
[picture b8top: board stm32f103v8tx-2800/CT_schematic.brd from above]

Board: 2 copper layers, 100.0 x 80.0 mm, 68 parts (0 on the bottom side), 46 nets, no tracks yet.

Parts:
C1, C10, C13, C14, C26: 1e-06; C0603
C2, C3, C4, C5, C6, C7: 1e-07; C0603
C8: 4.7e-06; C0603
C9: 1e-08; C0603
C11, C12, C21, C22, C23, C31: 1e-08; C0402
C15, C16, C17, C18, C19, C20, C28: 1e-07; C0402
C24: 1e-05; C1206
C25, C27: 1e-05; C1210
C29, C30: 0.0001; EXV-9H
F1: 240.0; L0603
J1: PJ-037B; PJ-037B_PACKAGE
R2, R14: 1000.0; R0603
R4: 4700.0; R0603
R5, R6: 2200.0; R0603
R7, R8, R9, R10, R18, R19: 10000.0; R0603
R11: 120.0; R0603
R12, R15, R17: 100000.0; R0603
R13: 2231.0; R0603
R16: 300000.0; R0603
R20: 9100.0; R0603
R21: 680000.0; R0603
R22: 120000.0; R0603
U1: stm32f103v8t7; LQFP100
U2: AT25160B-SSHL-T; SOIC-8
U3: 24AA02T-I/MNY; TDFN-8/6MM
U4: MCP2562-E/SN; SOIC-8
U5, U7: 182-009-113R531; 182-009-MALE
U6: SP3203ECY-L/TR; TSSOP20-I
U8: ASEK-32.768KHz-ECST; ASEK
U9: ASFL1-25MHZ-NCS; ASFL1
U10: LP3878SDX-ADJ/NOPB; WSON-8
U11: LP2951ACSDX/NOPB; WSON-8
U12: TPS3895ADRYR; SON-6
U13: 4-1437565-2; SW_4-1437565-2
U14: Q65110A2395; LGM67K-G1J2-24-Z
U15: nc7sz125m5x; NC7SZ125M5X

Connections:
CLK_U1_8: U1.8, U8.3
CLK_U1_12: U1.12, U9.3
GND: C1.2, C2.2, C3.2, C4.2, C5.2, C6.2, C7.2, C8.2, C9.2, C10.2, C11.2, C12.2, C13.2, C14.2, C15.2, C16.2, C19.2, C20.2, C21.2, C22.2, C23.2, C24.2, C25.2, C26.2, C27.2, C28.2, C29.2, C30.2, C31.2, J1.2, R2.2, R7.2, R14.2, R17.2, R20.2, R22.2, U1.10, U1.19, U1.20, U1.27, U1.49, U1.74, U1.99, U2.4, U3.4, U3.7, U4.2, U4.8, U5.5, U6.18, U7.5, U8.2, U9.2, U10.3, U10.PAD, U11.3, U11.4, U11.PAD, U12.2, U14.C, U15.1, U15.3
NET_U1_14: R4.1, U1.14, U15.4
NET_U1_22: C9.1, C10.1, F1.1, U1.21, U1.22
NET_U1_92: R5.1, U1.92, U3.6
NET_U1_93: R6.1, U1.93, U3.5
NET_U1_94: R7.1, U1.94
NET_U1_98: U13.3, U13.4
NET_U2_3: R8.1, U2.3
NET_U2_7: R10.1, U2.7
NET_U4_6: R11.2, U4.6
NET_U5_2: R11.2, U4.6, U5.2
NET_U5_3: R11.1, U4.7, U5.3
NET_U6_1: C17.1, U6.1
NET_U6_2: C19.1, U6.2
NET_U6_3: C17.2, U6.3
NET_U6_4: C18.1, U6.4
NET_U6_5: C18.2, U6.5
NET_U6_6: C20.1, U6.6
NET_U7_2: U6.14, U7.2
NET_U7_3: U6.17, U7.3
NET_U7_7: U6.13, U7.7
NET_U7_8: U6.16, U7.8
NET_U10_1: C23.1, U10.1
NET_U10_6: R13.2, R14.1, U10.6
NET_U10_8: R12.1, U10.8
NET_U11_5: R15.1, U11.5
NET_U11_7: R16.2, R17.1, U11.7
NET_U12_1: R19.1, R20.1, U12.1
NET_U12_3: R21.2, R22.1, U12.3
NET_U12_4: R18.1, U12.4, U15.2
NET_U13_1: R2.1, U13.1, U13.2
PROC_CAN_RX: U1.81, U4.4
PROC_CAN_TX: U1.82, U4.1
PROC_SPI1_MISO: U1.31, U2.2
PROC_SPI1_MOSI: U1.32, U2.5
PROC_SPI1_NSS: R9.1, U1.29, U2.1
PROC_SPI1_SCK: U1.30, U2.6
PROC_USART1_CTS: U1.70, U6.8
PROC_USART1_RTS: U1.71, U6.10
PROC_USART1_RX: U1.69, U6.11
PROC_USART1_TX: U1.68, U6.7
VCC_S1_10V7: C24.1, C26.1, C29.1, C30.1, J1.1, R12.2, U10.4, U11.8
VCC_TIER1_3V3: C1.1, C2.1, C3.1, C4.1, C5.1, C6.1, C7.1, C8.1, C11.1, C12.1, C14.1, C15.1, C16.1, C21.1, C22.1, C25.1, C28.1, C31.1, F1.2, R4.2, R5.2, R6.2, R8.2, R9.2, R10.2, R13.1, R18.2, R19.2, R21.1, U1.6, U1.11, U1.28, U1.50, U1.75, U1.100, U2.8, U3.8, U4.5, U6.12, U6.19, U8.4, U9.4, U10.5, U12.6, U15.5
VCC_TIER1_5V0: C13.1, C27.1, R15.2, R16.1, U4.3, U11.1
